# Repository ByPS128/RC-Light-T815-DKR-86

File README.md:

# RC-Light Controller for T815-DKR-86

## Introduction

RC-Light Controller is a sophisticated system for controlling the lighting of RC models, specifically designed for the 1:12 scale Tatra 815 1986 DAKAR model. This project combines hardware and software solutions to create a realistic and fully functional lighting system for RC models.

## Prerequisites
The control system assumes the use of an RC pistol transmitter with a steering wheel and at least 3 channels.
1. Channel for steering
2. Channel for throttle/brake
3. Channel of button type or a lever with two states (e.g., start/stop, on/off)

For development purposes, I used an inexpensive RC transmitter: TURBO 2.4GHz 91803G-VT 3CH RC Transmitter.

## Outline

1. [Feature Overview](#feature-overview)
2. [System Architecture](#system-architecture)
3. [Main Components](#main-components)
4. [Configuration and Customization](#configuration-and-customization)
5. [Optimization and Efficiency](#optimization-and-efficiency)
6. [Hardware Connection](#hardware-connection)
7. [Installation and Usage](#installation-and-usage)
8. [Project Structure and File Description](#project-structure-and-file-description)

## Feature Overview

- Multiple lighting modes including daytime running lights in 3 levels, long-distance lights
- Dynamic brightness control
- Realistic brake and reverse lights
- Calibration of RC channels for precise control
- Signal loss detection and indication
- Programmable flashing sequences for various system states
- Powered by the model's battery pack, with the option to connect to an independent power source

- Turn signals - this feature is not implemented because I don't need turn signals for the Dakar model. However, it's not difficult to program them. With the architecture I've designed, it's straightforward. If you're reading this and want turn signals but Arduino or C++ isn't your forte, write to me and I'll program it for you.

## System Architecture

The system is built on the Arduino platform and uses an object-oriented approach for a modular and extensible design. Key classes include:

- `MainApp`: Central control class coordinating all components
- `LightsController`: Manages various lighting modes
- `RCChannel`: Processes input signals from the RC receiver
- `CalibrationManager`: Ensures accurate calibration of RC channels
- `LedBlinker`: Provides a flexible interface for programmable LED sequences

## Main Classes

### MainApp

This class serves as the main entry point of the application. It initializes all other components, processes button inputs, and coordinates the overall system behavior.

### LightsController

Manages various lighting modes and controls individual LEDs. Supports smooth transitions between modes and responds to braking and reversing.

### RCChannel

Processes input PWM signals from the RC receiver, provides calibrated values for precise control.

### CalibrationManager

Allows calibration of RC channels for optimal performance. Stores calibration data in EEPROM for permanent retention.

### LedBlinker

A flexible system for creating complex flashing sequences, used to indicate various system states.

## Configuration and Customization

The system can be easily customized by modifying constants in the `AppConstants.h` file. Key configurable parameters include:

- Pin mapping for various functions
- Timing and threshold values for button detection
- Calibration constants for RC signals

To customize lighting behavior, the `LightsController` class can be modified, especially the `LIGHT_MATRIX` which defines various lighting modes.

## Optimization and Efficiency

The project uses several techniques to optimize memory usage and performance:

- Use of `PROGMEM` for storing constants in flash memory
- Efficient use of EEPROM for storing calibration data
- Optimized timing in the main loop to reduce power consumption
- Modular design allowing easy disabling of unused features

## Hardware Connection

The project includes a wiring diagram created in KiCad, providing a detailed view of the system's hardware configuration. The diagram includes the connection of Arduino Nano, RC receiver, LEDs, and other components.

I used the following key components to achieve the goal:

- Arduino Nano - main control unit
- Isolation module with optocoupler - detects motor rotation direction, necessary for movement direction detection
- PWM MOSFET module - creates PWM modulated signal on a separate circuit
- Step-down converter to 5V - powers Arduino and other peripherals
- LEDs .. describe types and properties
- Resistors .. describe quantities and values
- Capacitors .. describe quantities and values
- Transistors .. describe quantities and values
- Other components .. describe quantities and values

## Installation and Usage

1. Upload the code to Arduino Nano
2. Connect the hardware according to the provided diagram
3. Perform RC channel calibration using the built-in calibration mode
4. The system is ready for use - control the lighting using the RC transmitter

For detailed installation and usage instructions, see [documentation](./docs/USAGE.md).

---

This project represents a comprehensive and professional solution for controlling RC model lighting. Thanks to its modular design, efficient memory management, and flexible configuration, the RC-Light Controller is an ideal platform for modelers seeking realistic lighting for their RC models.

## Project Structure and File Description

### RC-Light-T815-DKR-86.ino
The main Arduino project file. Contains `setup()` and `loop()` functions that initialize and control the entire application. Creates an instance of `MainApp` and calls its methods for initialization and updating.

### AppConstants.h
File containing important constants used throughout the application. Defines pin mapping, EEPROM addresses, limits for RC signal validation, and other configuration values. Centralizing these constants facilitates maintenance and customization of the application.

### MainApp.h and MainApp.cpp
Defines the `MainApp` class, which serves as the central control unit for the entire application. Coordinates all other components, processes button inputs, and controls overall system behavior. Implements interfaces for processing button events and LED blinkers.

### RCChannel.h and RCChannel.cpp
The `RCChannel` class represents one channel of the RC receiver. Processes input PWM signals, performs calibration, and provides methods for obtaining current channel values. It is crucial for precise model control.

### CalibrationManager.h and CalibrationManager.cpp
`CalibrationManager` manages the RC channel calibration process. Allows saving and loading calibration data from EEPROM, ensuring that calibration is preserved even after power off.

### LightsController.h and LightsController.cpp
`LightsController` controls various lighting modes of the model. Manages switching between modes, controls individual LEDs, and responds to vehicle state (braking, reversing). Implements logic for various light configurations.

### ButtonBase.h and ButtonBase.cpp
The base class `ButtonBase` provides general functionality for processing button events. Implements detection of various press types (short, long, double) and a system for registering and notifying event subscribers.

### DigitalPullUpButton.h and DigitalPullUpButton.cpp
`DigitalPullUpButton` is a specialized class for working with digital buttons using Arduino's internal pull-up resistors. Inherits from `ButtonBase` and implements specific logic for detecting button presses.

### RcPwmButton.h and RcPwmButton.cpp
`RcPwmButton` is a class derived from `ButtonBase` that interprets PWM signal from the RC receiver as a button state. Allows using an RC channel as a virtual button.

### LedBlinker.h and LedBlinker.cpp
The `LedBlinker` class provides a flexible system for creating various LED blinking sequences. It is used to indicate various system states, such as calibration or signal loss.

### RCSteeringHandler.h and RCSteeringHandler.cpp
`RCSteeringHandler` processes input signals for steering wheel tracking. Implements logic for mapping input values to output actions, including LED brightness setting.

### RCThrottleHandler.h and RCThrottleHandler.cpp
`RCThrottleHandler` processes input signals for tracking the position of the throttle/brake lever. Detects states such as braking and provides this data to other components.

### SignalValidator.h and SignalValidator.cpp
The `SignalValidator` class checks the validity of RC signals. Verifies signal presence and pulse width validity for all RC channels, ensuring control reliability.

### NoiseFilter.h and NoiseFilter.cpp
`NoiseFilter` implements an algorithm for filtering noise in digital signals. Helps eliminate false triggers caused by electrical interference.

### cli.bat
A batch file for Windows that facilitates project compilation using Arduino CLI. Installs necessary libraries and runs compilation for Arduino Nano including cache clearing.

Each of these files plays an important role in the overall architecture of the project, contributing to its modularity, extensibility, and easy maintenance. Together, they create a robust system for controlling RC model lighting with advanced features such as calibration, signal loss detection, and flexible programming of light sequences.

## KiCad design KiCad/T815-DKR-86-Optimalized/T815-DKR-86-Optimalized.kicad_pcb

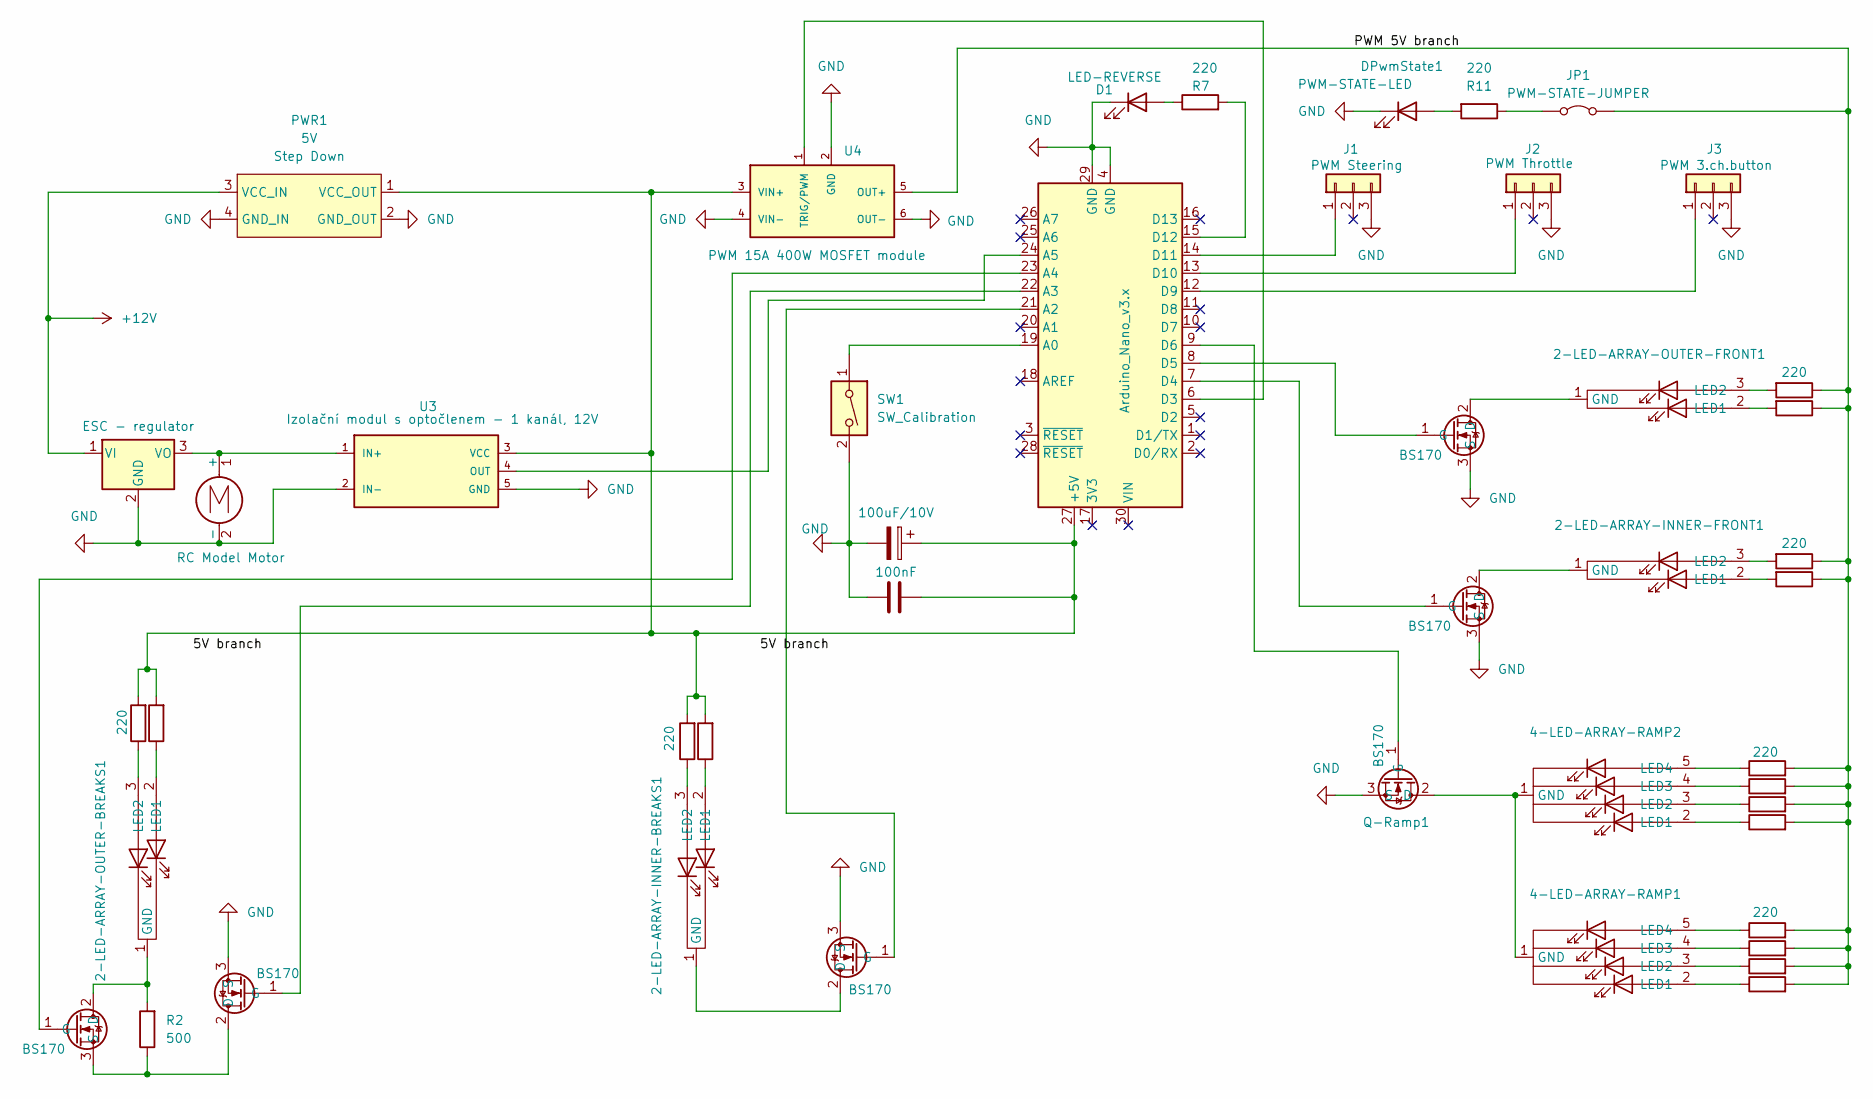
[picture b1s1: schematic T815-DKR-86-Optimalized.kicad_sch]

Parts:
2-LED-ARRAY-INNER-BREAKS1, 2-LED-ARRAY-INNER-FRONT1, 2-LED-ARRAY-OUTER-BREAKS1, 2-LED-ARRAY-OUTER-FRONT1: JST_XH_B3B-XH-A_1x03_P2.50mm_Vertical
4-LED-ARRAY-RAMP1, 4-LED-ARRAY-RAMP2: JST_XH_B5B-XH-A_1x05_P2.50mm_Vertical
A1: Arduino_Nano_v3.x; Arduino_Nano
C1: 100uF/10V; CP_Radial_D6.3mm_P2.50mm
C2: 100nF; CP_Radial_Tantal_D4.5mm_P2.50mm
D1: LED-REVERSE; JST_XH_B2B-XH-A_1x02_P2.50mm_Vertical
DPwmState1: PWM-STATE-LED; LED_D2.0mm_W4.8mm_H2.5mm_FlatTop
J1: PWM Steering; PinHeader_1x03_P2.54mm_Vertical
J2: PWM Throttle; PinHeader_1x03_P2.54mm_Vertical
J3: PWM 3.ch.button; PinHeader_1x03_P2.54mm_Vertical
JP1: PWM-STATE-JUMPER
M1: RC Model Motor; SolderWire-0.15sqmm_1x02_P4mm_D0.5mm_OD1.5mm
PWR1: 5V; SolderWire-0.15sqmm_1x02_P4mm_D0.5mm_OD1.5mm
Q1, Q3, Q4: BS170; BS170-TO-92L_Inline_Wide
Q6, Q7: BS170; TO-92L_Inline_Wide
Q-Ramp1: BS170; BS170-TO-92L_Inline_Wide
R1, R3, R5, R6, R7, R8, R9, R10, R11, R12, R13, R14, R15, R16, R17, R18, R19, R20: 220; R_Axial_DIN0204_L3.6mm_D1.6mm_P2.54mm_Vertical
R2: 500; R_Axial_DIN0204_L3.6mm_D1.6mm_P2.54mm_Vertical
SW1: SW_Calibration; LED_D2.0mm_W4.8mm_H2.5mm_FlatTop
U1: ESC - regulator
U3: Optocoupler_Module; Izolační modul s optočlenem
U4: PWM_MOSFET_Module; PWM-Module

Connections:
/PWM 5V branch: JP1.2 (B), R8.2, R9.2, R10.2, R12.2, R13.2, R14.2, R15.1, R16.1, R17.1, R18.1, R19.2, R20.2, U4.5 (OUT+)
GND: A1.4 (GND), A1.29 (GND), C1.2, C2.1, D1.1 (K), DPwmState1.1 (K), J1.3, J2.3, J3.3, M1.2 (-), PWR1.2 (GND_OUT), PWR1.4 (GND_IN), Q3.3 (S), Q4.3 (S), Q6.3 (S), Q7.3 (S), Q-Ramp1.3 (S), SW1.2, U1.2 (GND), U3.2 (IN-), U3.5 (GND), U4.2 (GND), U4.4 (VIN-), U4.6 (OUT-)
unnamed: 2-LED-ARRAY-INNER-BREAKS1.1 (GND), Q4.2 (D)
unnamed: 2-LED-ARRAY-INNER-BREAKS1.2 (LED1), R6.1
unnamed: 2-LED-ARRAY-INNER-BREAKS1.3 (LED2), R5.1
unnamed: 2-LED-ARRAY-INNER-FRONT1.1 (GND), Q7.2 (D)
unnamed: 2-LED-ARRAY-INNER-FRONT1.2 (LED1), R18.2
unnamed: 2-LED-ARRAY-INNER-FRONT1.3 (LED2), R17.2
unnamed: 2-LED-ARRAY-OUTER-BREAKS1.1 (GND), Q1.2 (D), R2.2
unnamed: 2-LED-ARRAY-OUTER-BREAKS1.2 (LED1), R3.1
unnamed: 2-LED-ARRAY-OUTER-BREAKS1.3 (LED2), R1.1
unnamed: 2-LED-ARRAY-OUTER-FRONT1.1 (GND), Q6.2 (D)
unnamed: 2-LED-ARRAY-OUTER-FRONT1.2 (LED1), R16.2
unnamed: 2-LED-ARRAY-OUTER-FRONT1.3 (LED2), R15.2
unnamed: 4-LED-ARRAY-RAMP1.1 (GND), 4-LED-ARRAY-RAMP2.1 (GND), Q-Ramp1.2 (D)
unnamed: 4-LED-ARRAY-RAMP1.2 (LED1), R13.1
unnamed: 4-LED-ARRAY-RAMP1.3 (LED2), R14.1
unnamed: 4-LED-ARRAY-RAMP1.4 (LED3), R19.1
unnamed: 4-LED-ARRAY-RAMP1.5 (LED4), R20.1
unnamed: 4-LED-ARRAY-RAMP2.2 (LED1), R8.1
unnamed: 4-LED-ARRAY-RAMP2.3 (LED2), R9.1
unnamed: 4-LED-ARRAY-RAMP2.4 (LED3), R10.1
unnamed: 4-LED-ARRAY-RAMP2.5 (LED4), R12.1
unnamed: A1.27 (+5V), C1.1, C2.2, PWR1.1 (VCC_OUT), R1.2, R3.2, R5.2, R6.2, U3.3 (VCC), U4.3 (VIN+)
unnamed: A1.19 (A0), SW1.1
unnamed: A1.21 (A2), Q4.1 (G)
unnamed: A1.22 (A3), Q3.1 (G)
unnamed: A1.23 (A4), Q1.1 (G)
unnamed: A1.24 (A5), U3.4 (OUT)
unnamed: A1.6 (D3), U4.1 (TRIG/PWM)
unnamed: A1.7 (D4), Q7.1 (G)
unnamed: A1.8 (D5), Q6.1 (G)
unnamed: A1.9 (D6), Q-Ramp1.1 (G)
unnamed: A1.12 (D9), J3.1
unnamed: A1.13 (D10), J2.1
unnamed: A1.14 (D11), J1.1
unnamed: A1.15 (D12), R7.2
unnamed: D1.2 (A), R7.1
unnamed: DPwmState1.2 (A), R11.2
unnamed: JP1.1 (A), R11.1
unnamed: M1.1 (+), U1.3 (VO), U3.1 (IN+)
unnamed: Q1.3 (S), Q3.2 (D), R2.1
unnamed: PWR1.3 (VCC_IN), U1.1 (VI)

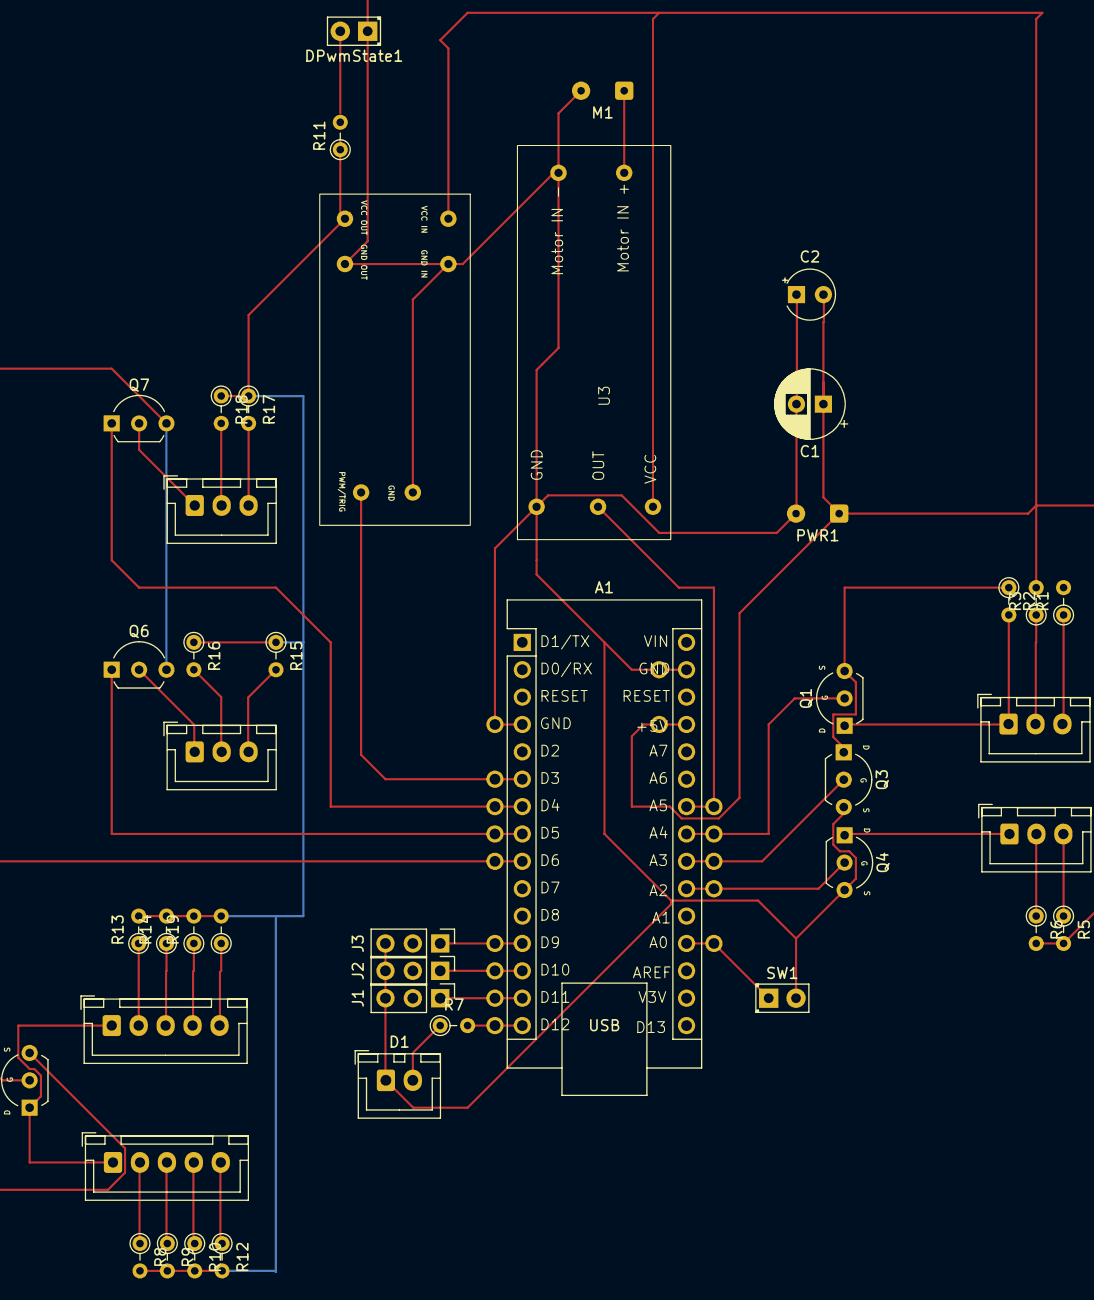
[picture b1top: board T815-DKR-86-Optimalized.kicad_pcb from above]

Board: 2 copper layers, 44 parts (0 on the bottom side), 41 nets.

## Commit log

2024-01-27 initial state
2024-01-27 +readme
2024-01-28 Button press resolving, button reactions, programming methods - calibrate and adjust.
2024-01-28 formatting
2024-01-28 values and datatypes refactor to use proepr ranges
2024-01-28 removing commented code
2024-01-28 Added LightsController which constrolls which leds will be turned on or off and at which brightness lkevel.
2024-01-28 Added support to detect signal lost.
2024-01-29 Bug fixing in led setup led output settings.
    Changes in pins configuration to leave as much as possible of PWM pins.
2024-01-30 Added code for reading motor polarity and revs.
    Implemented potentiometer simulator of opto-isolators and fake driver for them.
2024-01-30 Bug fix, restore lights mode after signal of receiver is restored.
2024-01-30 enabled storing data to eprom.
2024-02-05 naming refactor, addes a few comments.
    Also changed pub/sub pattern implementetion.
2024-07-16 working on schematic
2024-07-17 Relevant version using mosfets.
2024-07-17 cosmetic changes in layout.
2024-07-17 Rendered version of schema
2024-07-21 break updates
2024-07-21 working version against to schema
2024-07-21 better threshold for reverse detection
2024-07-22 refactor names of constants
2024-07-23 added comments
2024-07-23 Removing dependency on information that motor is spinning forward. Thes light module does not need that information.
2024-07-23 Simplification of signal evaluation.
2024-07-24 revised version. corrected transistors connections.
2024-07-24 Schema revision 2
2024-07-27 get ready for more clever button class
2024-07-27 lettle refactor of rc pwm button
2024-07-27 new button base class and reimplemented rc pwm button
2024-07-27 added new digital pull up button class and attached one instance on A0 as temporary demo
2024-07-31 Naive implemented files, need to integrate to the project.
2024-07-31 new version of schema using new schematic layouts to be able make good pcb layout. Typicaly led arrays are realies as connector with common ground, not a many plus and minus wires.
2024-07-31 Better calibration.
2024-08-07 functional calibration and rc channel signal detection.
2024-08-07 Refactored calibration and the way of store/restore eprom calibration data
2024-08-07 Buttons refactored for better and more logical usage.
2024-08-07 Bug fix at PwmRcButton + enabled whole application.
2024-08-07 Throttle handler refactor, it uses rc channel instane now.
2024-08-07 reformat sources
2024-08-07 little clean up
2024-08-07 logic refactor, fien tune of brightness setup process.
2024-08-07 clean up, removed unused constants
2024-08-07 led animators refactor
2024-08-07 bug fix reading eprom
2024-08-07 removed debug prints in initialization method.
2024-08-08 memory saving optimalizations (partial, not all possible).
2024-08-08 led blinker allows setup PWM led brightness for each step of animation. So fading effects are now supported.
2024-08-08 removed unused declarations
2024-08-08 some functions is inlined now
2024-08-13 schema update - rearanged pins.
2024-08-20 schema update - pcb more optima use of arduino pins
2024-08-22 none
2024-09-01 Changed pins numbers usage to respond with physical HW layout.
2024-09-02 extended readme in cs
2024-09-02 removing obsoleted files
2024-09-02 translated reame
